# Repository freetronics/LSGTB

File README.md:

LibreSat Ground Test Breakout
=============================
Copyright 2015 Freetronics Pty Ltd  
Freetronics site:  www.freetronics.com  
Freetronics email: info@freetronics.com  

FIXME

Features:

 * FIXME

More information is available at:

  http://www.freetronics.com.au/lsgtb

INSTALLATION
------------
The design is saved as an EAGLE project. EAGLE PCB design software is
available from www.cadsoftusa.com free for non-commercial use. To use
this project download it and place the directory containing these files
into the "eagle" directory on your computer. Then open EAGLE and
navigate to Projects -> eagle -> LSGTB.

DISTRIBUTION
------------
The specific terms of distribution of this project are governed by the
license referenced below.

LICENSE
-------
Licensed under the TAPR Open Hardware License (www.tapr.org/OHL).
The "license" folder within this repository also contains a copy of
this license in plain text format.

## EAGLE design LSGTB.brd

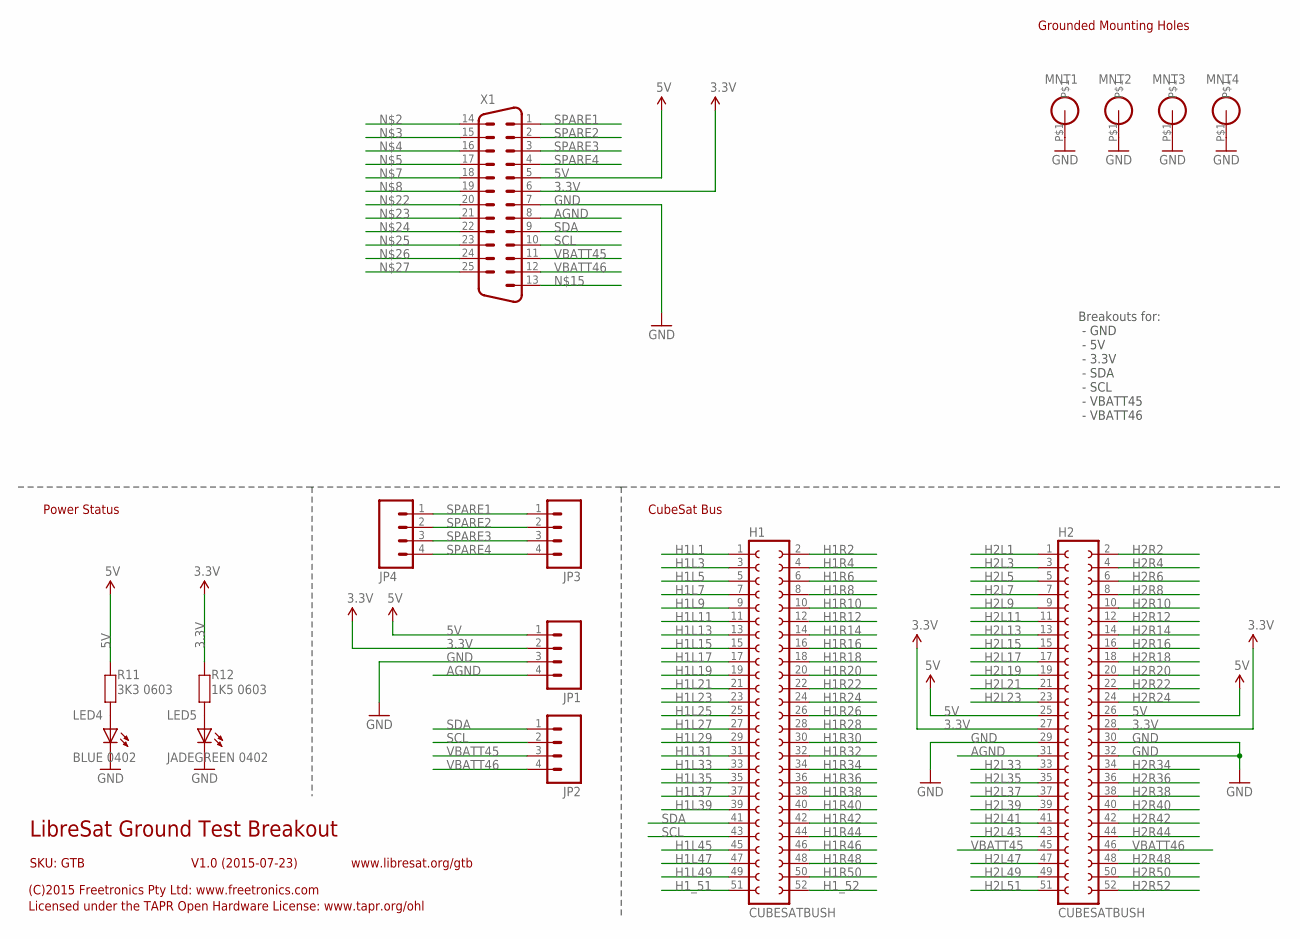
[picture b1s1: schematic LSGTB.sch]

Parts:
H1, H2: CUBESATBUSH; CUBESATBUS
JP1, JP2, JP3: M04SCREW; SCREWTERMINAL-3.5MM-4
JP4: M04PTH; 1X04
LED4: BLUE 0402; LED-0603
LED5: JADEGREEN 0402; LED-0603
MNT1, MNT2, MNT3, MNT4: HOLE3.2MM; HOLE32
R11: 3K3 0603; 0603
R12: 1K5 0603; 0603
X1: DB25HP; M25HP

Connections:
3.3V: H2.27, H2.28, JP1.2, R12.1, X1.6
5V: H2.25, H2.26, JP1.1, R11.1, X1.5
AGND: H2.31, JP1.4, X1.8
GND: H2.29, H2.30, H2.32, JP1.3, LED4.C, LED5.C, MNT1.P$1, MNT2.P$1, MNT3.P$1, MNT4.P$1, X1.7
H1L1: H1.1
H1L3: H1.3
H1L5: H1.5
H1L7: H1.7
H1L9: H1.9
H1L11: H1.11
H1L13: H1.13
H1L15: H1.15
H1L17: H1.17
H1L19: H1.19
H1L21: H1.21
H1L23: H1.23
H1L25: H1.25
H1L27: H1.27
H1L29: H1.29
H1L31: H1.31
H1L33: H1.33
H1L35: H1.35
H1L37: H1.37
H1L39: H1.39
H1L45: H1.45
H1L47: H1.47
H1L49: H1.49
H1R2: H1.2
H1R4: H1.4
H1R6: H1.6
H1R8: H1.8
H1R10: H1.10
H1R12: H1.12
H1R14: H1.14
H1R16: H1.16
H1R18: H1.18
H1R20: H1.20
H1R22: H1.22
H1R24: H1.24
H1R26: H1.26
H1R28: H1.28
H1R30: H1.30
H1R32: H1.32
H1R34: H1.34
H1R36: H1.36
H1R38: H1.38
H1R40: H1.40
H1R42: H1.42
H1R44: H1.44
H1R46: H1.46
H1R48: H1.48
H1R50: H1.50
H1_51: H1.51
H1_52: H1.52
H2L1: H2.1
H2L3: H2.3
H2L5: H2.5
H2L7: H2.7
H2L9: H2.9
H2L11: H2.11
H2L13: H2.13
H2L15: H2.15
H2L17: H2.17
H2L19: H2.19
H2L21: H2.21
H2L23: H2.23
H2L33: H2.33
H2L35: H2.35
H2L37: H2.37
H2L39: H2.39
H2L41: H2.41
H2L43: H2.43
H2L47: H2.47
H2L49: H2.49
H2L51: H2.51
H2R2: H2.2
H2R4: H2.4
H2R6: H2.6
H2R8: H2.8
H2R10: H2.10
H2R12: H2.12
H2R14: H2.14
H2R16: H2.16
H2R18: H2.18
H2R20: H2.20
H2R22: H2.22
H2R24: H2.24
H2R34: H2.34
H2R36: H2.36
H2R38: H2.38
H2R40: H2.40
H2R42: H2.42
H2R44: H2.44
H2R48: H2.48
H2R50: H2.50
H2R52: H2.52
unnamed: LED5.A, R12.2
unnamed: LED4.A, R11.2
SCL: H1.43, JP2.2, X1.10
SDA: H1.41, JP2.1, X1.9
SPARE1: JP3.1, JP4.1, X1.1
SPARE2: JP3.2, JP4.2, X1.2
SPARE3: JP3.3, JP4.3, X1.3
SPARE4: JP3.4, JP4.4, X1.4
VBATT45: H2.45, JP2.3, X1.11
VBATT46: H2.46, JP2.4, X1.12

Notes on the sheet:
CubeSat Bus
Power Status
Grounded Mounting Holes
LibreSat Ground Test Breakout
V1.0 (2015-07-23)
SKU: GTB
(C)2015 Freetronics Pty Ltd: www.freetronics.com
Licensed under the TAPR Open Hardware License: www.tapr.org/ohl
www.libresat.org/gtb
Breakouts for: - GND - 5V - 3.3V - SDA - SCL - VBATT45 - VBATT46

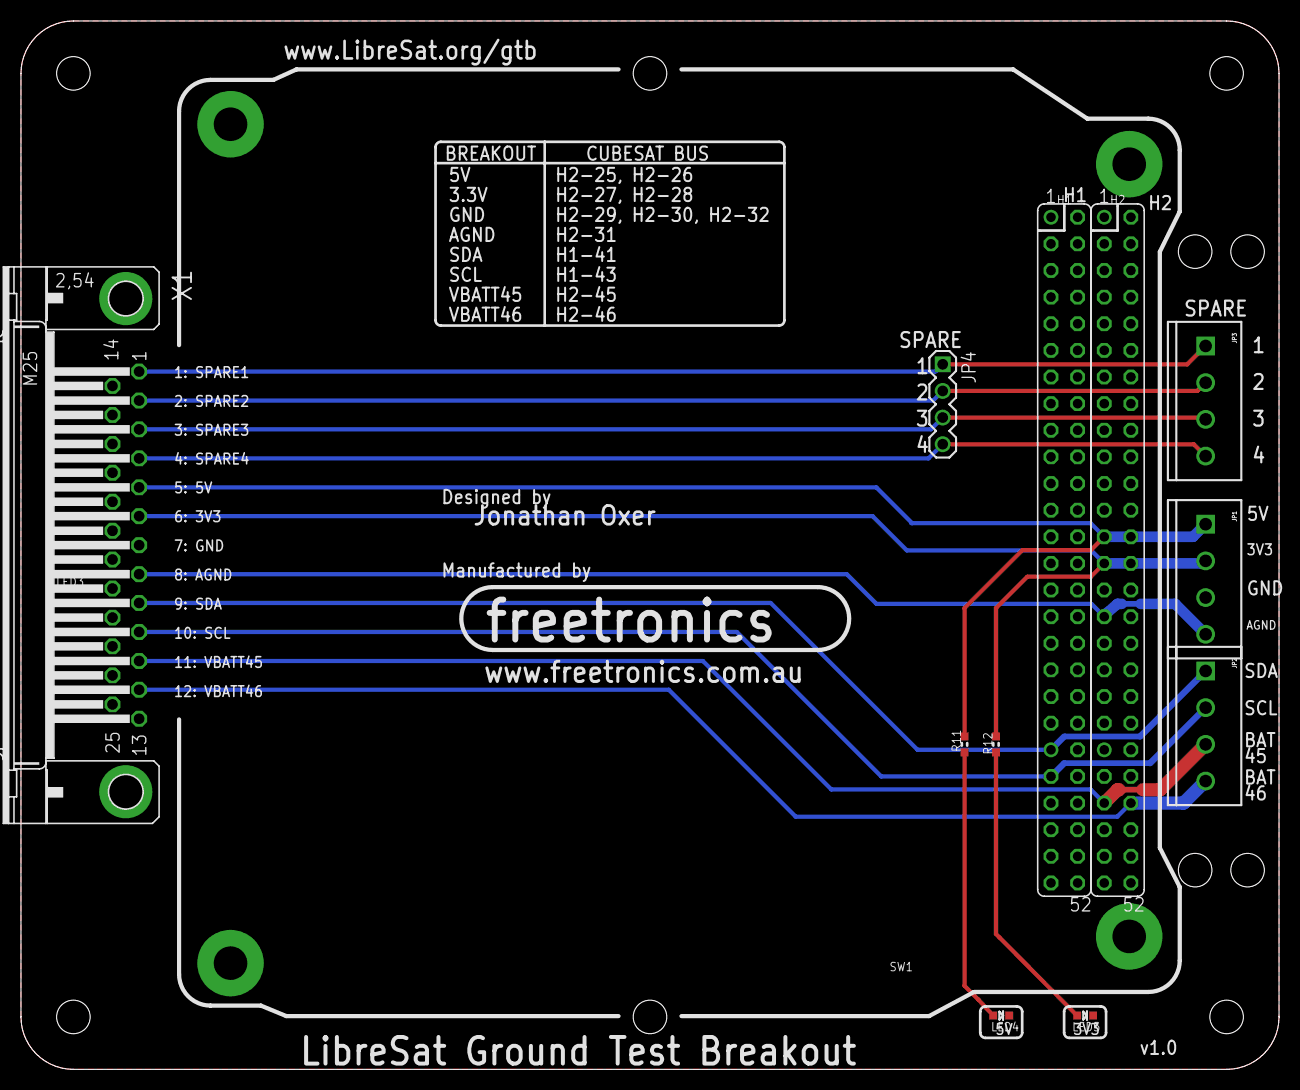
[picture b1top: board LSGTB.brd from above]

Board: 2 copper layers, 120.0 x 100.0 mm, 16 parts (1 on the bottom side), 14 nets.

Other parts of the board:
U$2: OSHW_10X200_NOTEXT

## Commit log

2015-08-17 Initial import

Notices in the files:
parts and their libraries:
freetronics-original: Licensing: CC v3.0 Share-Alike You are welcome to use this library for commercial purposes.
